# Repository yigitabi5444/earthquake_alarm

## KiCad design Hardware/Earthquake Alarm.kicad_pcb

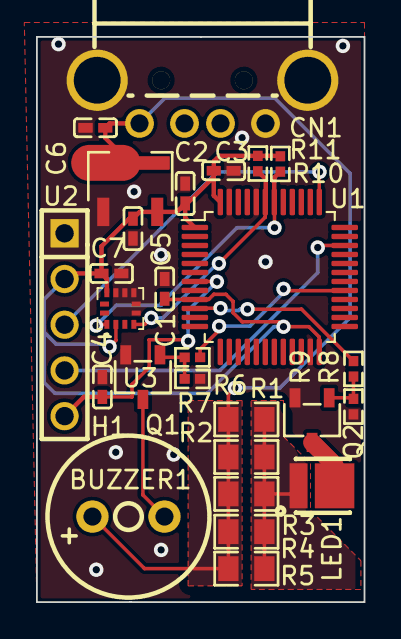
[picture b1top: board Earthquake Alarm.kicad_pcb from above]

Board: 2 copper layers, 18.2 x 31.4 mm, 27 parts (0 on the bottom side), 15 nets.

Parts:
BUZZER1: Buzzer 2-5V; BUZ-TH_BD9.0-P4.00-D0.6-FD
C1, C2, C3, C5, C6, C7: 1uF 25V; C0402
C4: 16V 100nF; C0402_NEW
CN1: USB Male; USB-A-TH_AM90
H1: Header 2.54 5P Female; HDR-TH_5P-P2.54-V-F
LED1: XL-3030UWC-1W-3V; LED-SMD_L3.0-W3.0_WHITE
Q1, Q2: AO3400A; SOT-23-3_L2.9-W1.6-P1.90-LS2.8-BR
R1, R2, R3, R4, R5: 33Ω; R0805
R6, R8: 100Ω 0402 50V; R0402
R7, R9, R10, R11: 10kΩ 0402 50V; R0402
U1: STM32F030C8Tx; LQFP-48_7x7mm_P0.5mm
U2: HT7533-1_C14289; SOT-89-3_L4.5-W2.5-P1.50-LS4.2-BR
U3: LIS2DH12TR; LGA-12_L2.0-W2.0-P0.50-BL

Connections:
+3.3V: C1.2, C2.2, C3.2, C5.2, C7.2, H1.2, R10.2, R11.2, U1.1 (VDD), U1.9 (VDDA), U1.24 (VDD), U1.48 (VDD), U2.3 (Vout), U3.2 (CS), U3.10 (VDD_IO)
+5V: BUZZER1.1, C6.2, CN1.1 (VCC), R1.2, R2.2, R3.2, R4.2, R5.2, U2.2 (Vin)
/Buzzer: R6.1, U1.29 (PA8)
/LED: R8.1, U1.10 (PA0)
/NRST: C4.2, H1.5, U1.7 (NRST)
/SCL: R10.1, U1.42 (PB6), U3.1 (SCL/SPC)
/SDA: R11.1, U1.43 (PB7), U3.4 (SDA/SDI/SDO)
/SWCLK: H1.3, U1.37 (PA14)
/SWDIO: H1.4, U1.34 (PA13)
GND: C1.1, C2.1, C3.1, C4.1, C5.1, C6.1, C7.1, CN1.4 (GND), CN1.MH1, CN1.MH2, H1.1, Q1.2 (S), Q2.2 (S), R7.1, R9.1, U1.8 (VSSA), U1.23 (VSS), U1.44 (BOOT0), U1.47 (VSS), U2.1 (GND), U3.5 (RES), U3.6 (GND), U3.7 (GND), U3.8 (GND), U3.9 (VDD)
unnamed: BUZZER1.2, Q1.3 (D)
unnamed: LED1.1 (A), R1.1, R2.1, R3.1, R4.1, R5.1
unnamed: LED1.2 (K), Q2.3 (D)
unnamed: Q1.1 (G), R6.2, R7.2
unnamed: Q2.1 (G), R8.2, R9.2

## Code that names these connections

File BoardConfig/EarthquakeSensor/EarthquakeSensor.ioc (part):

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Mcu.Name=STM32F030C8Tx
Mcu.Package=LQFP48
Mcu.UserName=STM32F030C8Tx
PA0.GPIOParameters=GPIO_Label
PA0.GPIO_Label=LED
PA0.Signal=GPIO_Output
PA13.Mode=Serial_Wire
PA13.Signal=SYS_SWDIO
PA14.Mode=Serial_Wire
PA14.Signal=SYS_SWCLK
PA8.GPIOParameters=GPIO_Label
PA8.GPIO_Label=BUZZER
PA8.Signal=S_TIM1_CH1
PB6.Mode=I2C
PB6.Signal=I2C1_SCL
PB7.Mode=I2C
PB7.Signal=I2C1_SDA
board=custom

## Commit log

2023-02-20 finished sch
2023-03-05 Finished USB based design
2023-03-06 changed usb connector
